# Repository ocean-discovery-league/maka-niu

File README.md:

# maka-niu

"Maka" - Eye, "Niu" - Coconut

Maka Niu, aka the "CocoCam,"  is a low-cost oceanographic camera and sensor platform that enables the exploration of undersea environments using a new pressure-tolerant camera housing and an all-natural, locally sourced, biodegradable buoyancy-control device. The coconut (Cocos nucifera ) can float for over 3,000 miles and still remain viable; as such, it makes an excellent organic platform for deploying scientific apparatus.

Maka Niu is a community-driven project that allows local groups to explore and monitor their marine resources. Based around off-the-shelf single-board computers and readily available microprocessors, Maka Niu is inexpensive to produce, easy to program, and simple to use. Designed as an open platform for scientific education and exploration, it will give classrooms and communities the ability to upload video and sensor data into FathomNet, a centralized database where machine learning algorithms assist with classification of marine species, seabed substrate identification, and accumulated time-series sensor data. This data will be publically available, allowing visualization, sharing, and discussion with policy makers from the local to global levels.

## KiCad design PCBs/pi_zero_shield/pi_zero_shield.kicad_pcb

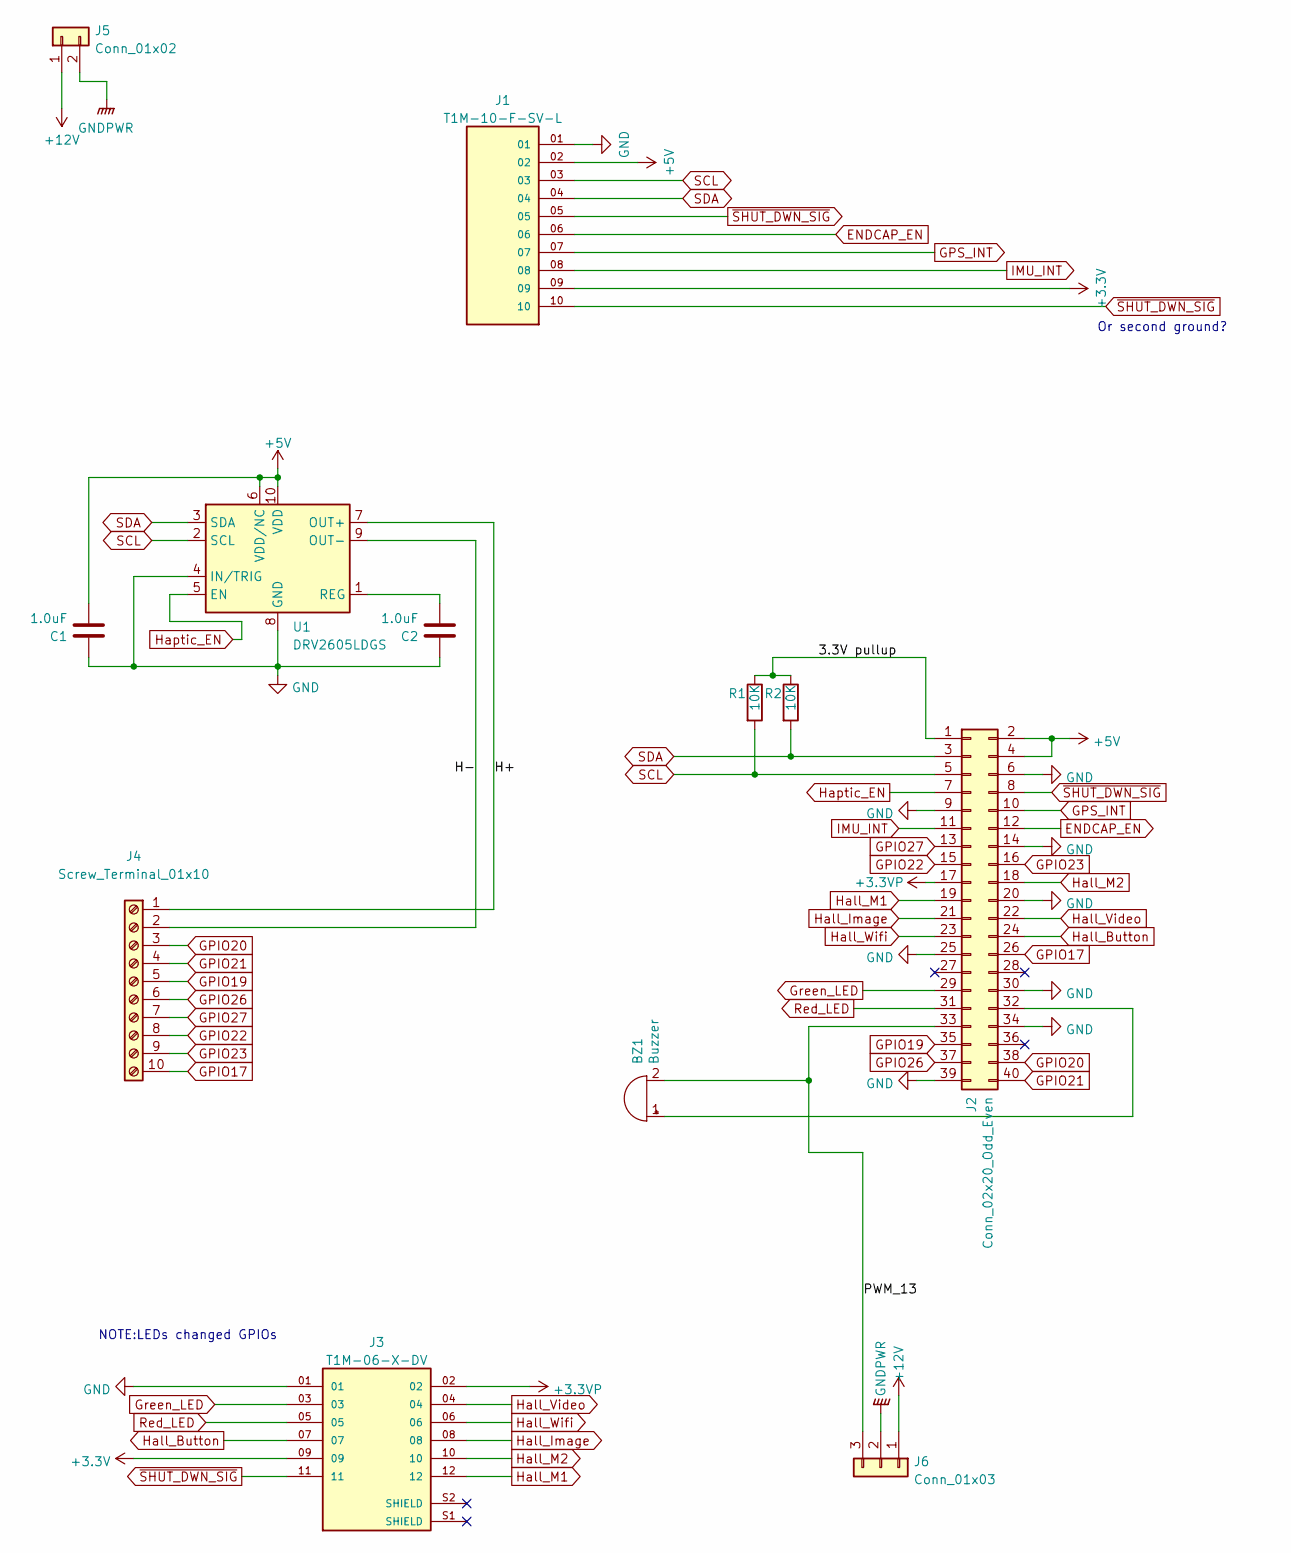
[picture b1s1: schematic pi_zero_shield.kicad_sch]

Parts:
BZ1: Buzzer; Buzzer_12x9.5RM7.6; LCSC C968749
C1, C2: 1.0uF; C_0603_1608Metric; LCSC C90540
J1: T1M-10-F-SV-L; SAMTEC_T1M-10-F-SV-L; Digikey SAM16035-ND
J2: Conn_02x20_Odd_Even; Pi_PinSocket_2x20; Digikey 952-3218-ND
J3: T1M-06-X-DV; SAMTEC_T1M-06-X-DV; Digikey -Get from Samtec
J4: Screw_Terminal_01x10; PinHeader_1x10_P2.54mm_Vertical; Digikey ED10567-ND
J5: Conn_01x02; Molex_Micro-Fit_3.0_43650-0210_1x02-1MP_P3.00mm_Horizontal; Digikey WM6264CT-ND
J6: Conn_01x03; Molex_Micro-Fit_3.0_43650-0310_1x03-1MP_P3.00mm_Horizontal; Digikey WM1886CT-ND
R1, R2: 10K; R_0603_1608Metric; LCSC C25804
U1: DRV2605LDGS; VSSOP-10_3x3mm_P0.5mm; LCSC C527464

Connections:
+3.3VP: J2.17, J3.02
+3V3: J1.09, J3.09
+5V: C1.1, J1.02, J2.2, J2.4, U1.6 (VDD/NC), U1.10 (VDD)
+12V: J5.1, J6.1
/3.3V pullup: J2.1, R1.1, R2.1
/H+: J4.1, U1.7 (OUT+)
/H-: J4.2, U1.9 (OUT-)
/PWM_13: BZ1.2 (+), J2.33, J6.3
ENDCAP_EN: J1.06, J2.12
GND: C1.2, C2.2, J1.01, J2.6, J2.9, J2.14, J2.20, J2.25, J2.30, J2.34, J2.39, J3.01, U1.4 (IN/TRIG), U1.8 (GND)
GNDPWR: J5.2, J6.2
GPIO17: J2.26, J4.10
GPIO19: J2.35, J4.5
GPIO20: J2.38, J4.3
GPIO21: J2.40, J4.4
GPIO22: J2.15, J4.8
GPIO23: J2.16, J4.9
GPIO26: J2.37, J4.6
GPIO27: J2.13, J4.7
GPS_INT: J1.07, J2.10
Green_LED: J2.29, J3.03
Hall_Button: J2.24, J3.07
Hall_Image: J2.21, J3.08
Hall_M1: J2.19, J3.12
Hall_M2: J2.18, J3.10
Hall_Video: J2.22, J3.04
Hall_Wifi: J2.23, J3.06
Haptic_EN: J2.7, U1.5 (EN)
IMU_INT: J1.08, J2.11
unnamed: BZ1.1 (-), J2.32
unnamed: C2.1, U1.1 (REG)
Red_LED: J2.31, J3.05
SCL: J1.03, J2.5, R1.2, U1.2 (SCL)
SDA: J1.04, J2.3, R2.2, U1.3 (SDA)
~SHUT_DWN_SIG: J1.05, J1.10, J2.8, J3.11

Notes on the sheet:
NOTE:LEDs changed GPIOs
Or second ground?

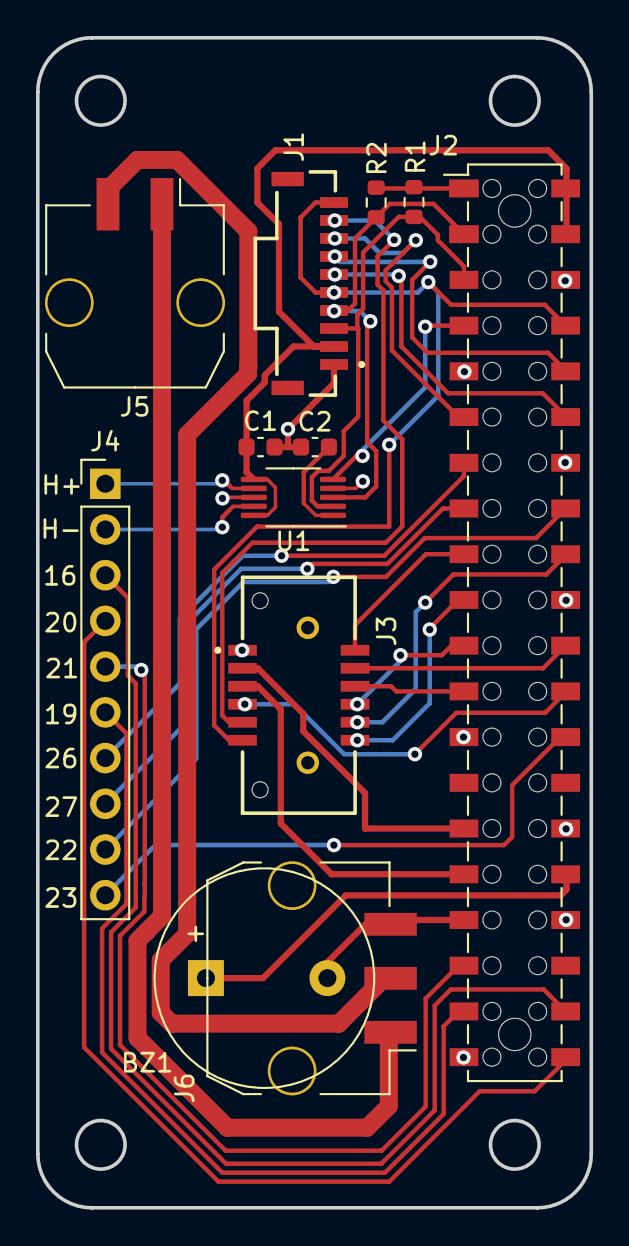
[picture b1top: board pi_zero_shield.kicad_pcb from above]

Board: 2 copper layers, 30.8 x 65.0 mm, 12 parts (0 on the bottom side), 35 nets.

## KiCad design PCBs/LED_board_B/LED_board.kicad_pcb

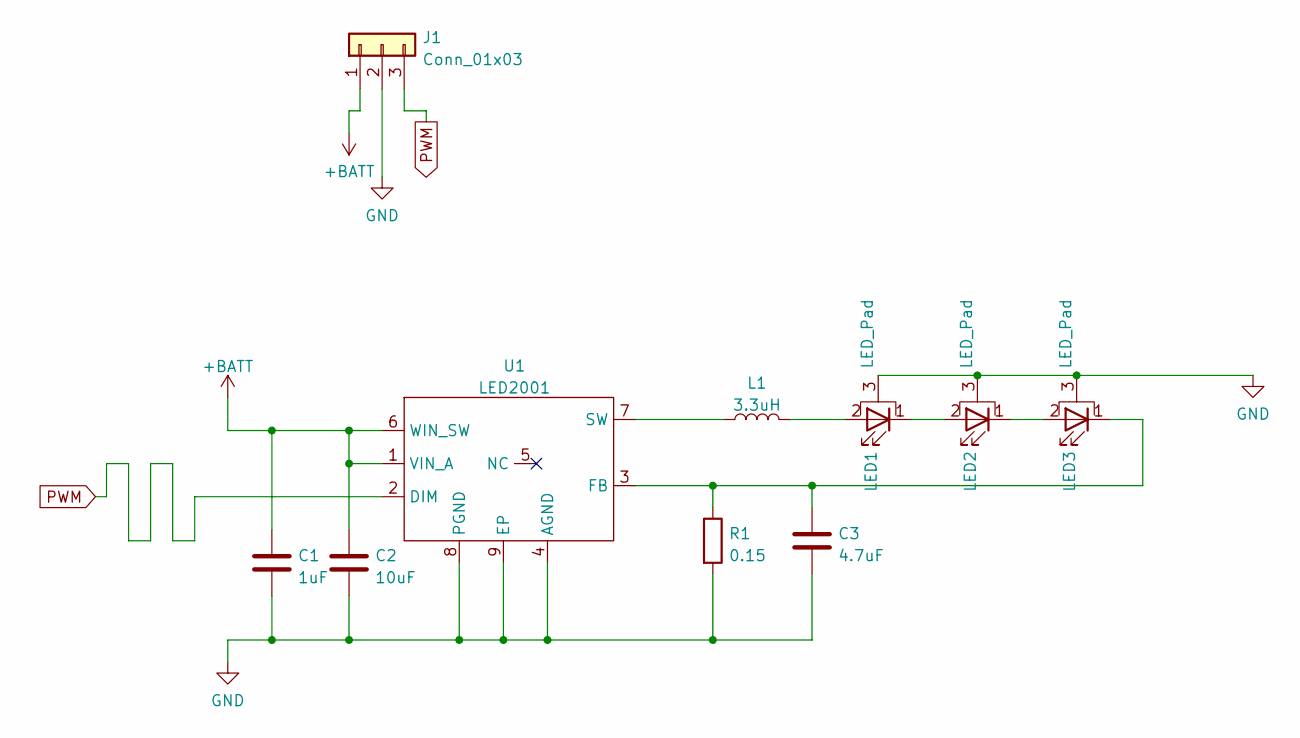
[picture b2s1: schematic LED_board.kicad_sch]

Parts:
C1: 1uF; C_0805_2012Metric; LCSC C28323
C2: 10uF; C_1210_3225Metric; LCSC C170073
C3: 4.7uF; C_1210_3225Metric; LCSC C384711
J1: Conn_01x03; Molex_Micro-Fit_3.0_43650-0324_1x03-1MP_P3.00mm_Vertical; Digikey WM3887CT-ND
L1: 3.3uH; ASWPA8050S; LCSC C340237
LED1, LED2, LED3: LED_Pad; LED_Cree-XHP50_6V; Digikey XMLBWT-00-0000-0000U2050CT-ND
R1: 0.15; R_2512_6332Metric; LCSC C176046
U1: LED2001; HSOP-8-1EP_3.9x4.9mm_P1.27mm_EP2.41x3.1mm; LCSC C2678918

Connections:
+BATT: C1.1, C2.1, J1.1, U1.1 (VIN_A), U1.6 (WIN_SW)
GND: C1.2, C2.2, C3.2, J1.2, LED1.3 (PAD), LED2.3 (PAD), LED3.3 (PAD), R1.2, U1.4 (AGND), U1.8 (PGND), U1.9 (EP)
unnamed: C3.1, LED3.1 (K), R1.1, U1.3 (FB)
unnamed: L1.1, U1.7 (SW)
unnamed: L1.2, LED1.2 (A)
unnamed: LED1.1 (K), LED2.2 (A)
unnamed: LED2.1 (K), LED3.2 (A)
PWM: J1.3, U1.2 (DIM)

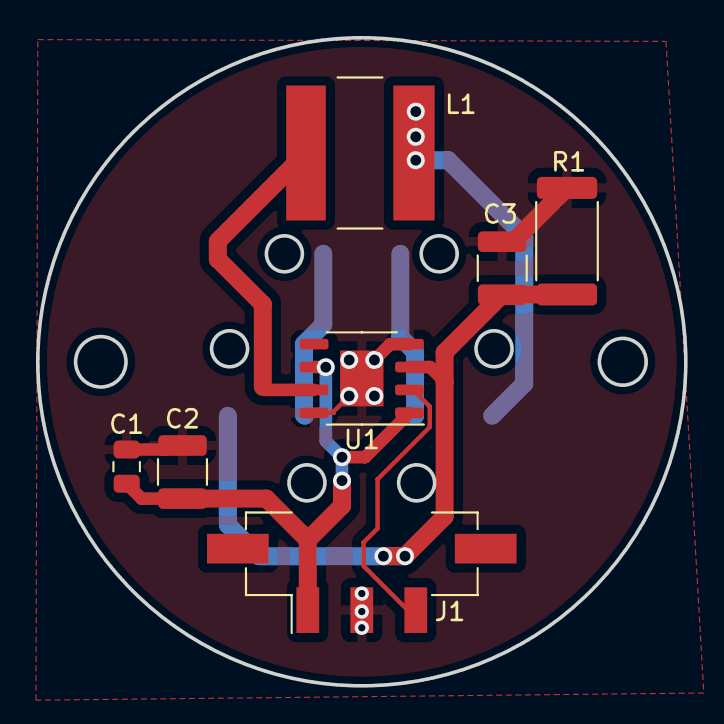
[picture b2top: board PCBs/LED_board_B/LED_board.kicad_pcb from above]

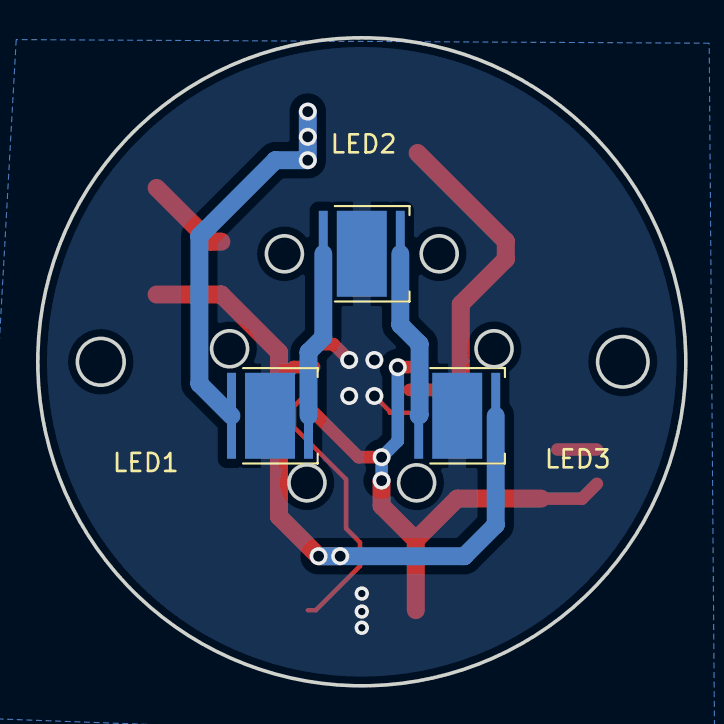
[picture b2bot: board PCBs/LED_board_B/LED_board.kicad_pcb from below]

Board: 2 copper layers, 36.0 x 36.0 mm, 10 parts (3 on the bottom side), 8 nets.

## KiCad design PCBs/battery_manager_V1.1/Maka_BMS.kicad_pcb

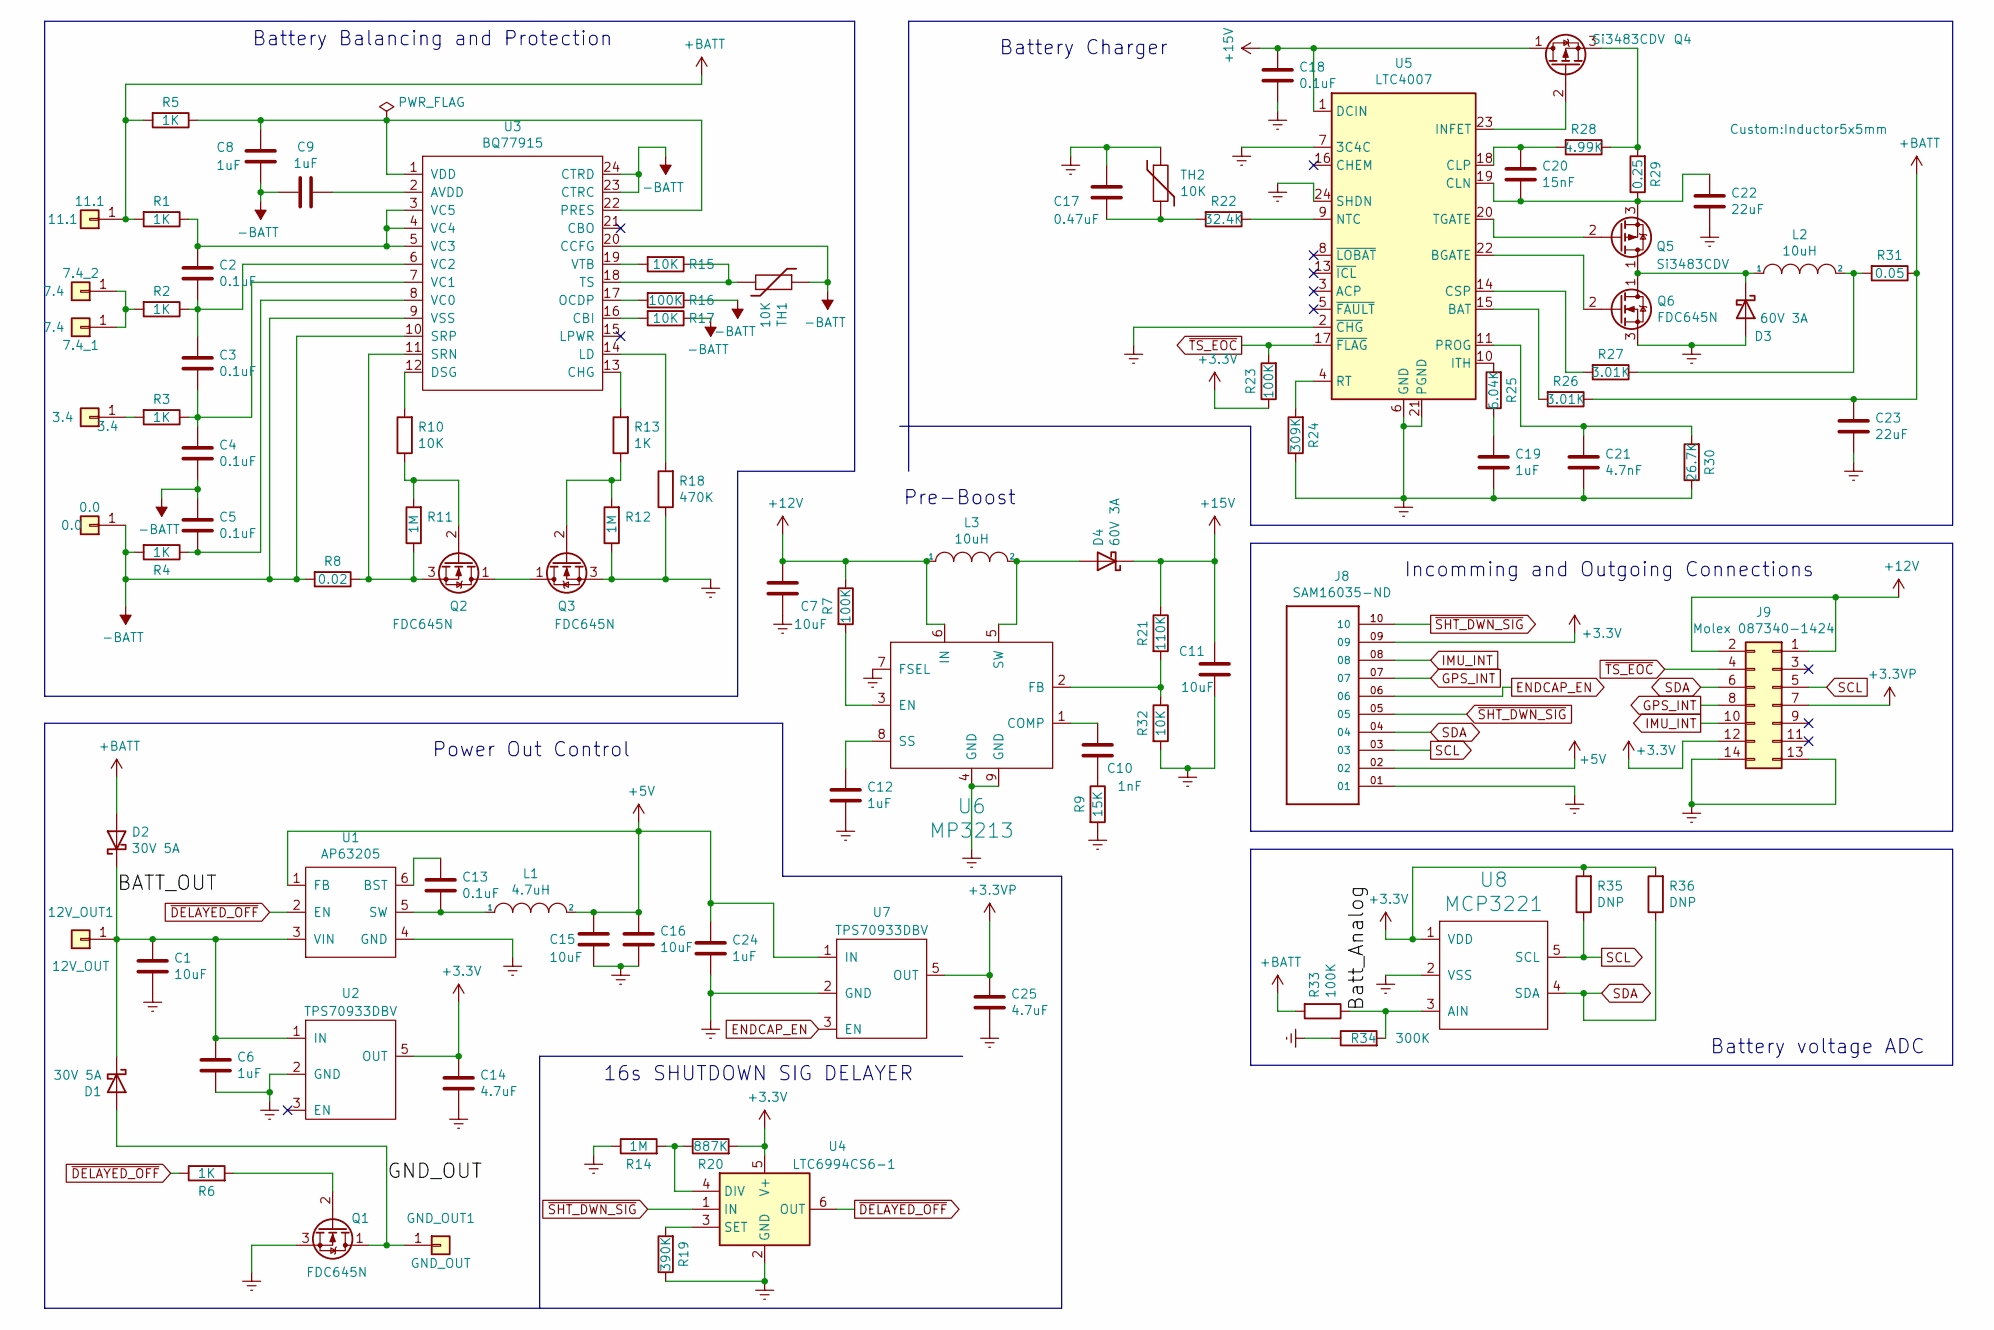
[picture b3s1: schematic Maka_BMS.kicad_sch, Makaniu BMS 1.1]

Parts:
0.0: 0.0; TruHole_Batter_Contact_Pad_with_9mm_clear; Digikey 36-240-ND
3.4: 3.4; TestPoint_THTPad_D1.5mm_Drill0.7mm
7.4_1, 7.4_2: 7.4; TruHole_Batter_Contact_Pad_with_9mm_clear; Digikey 36-240-ND
11.1: 11.1; TestPoint_THTPad_D1.5mm_Drill0.7mm
12V_OUT1: 12V_OUT; TestPoint_THTPad_D1.5mm_Drill0.7mm
C1, C7, C11, C15, C16: 10uF; C_0603_1608Metric; Digikey 490-7202-1-ND
C2, C3, C4, C5, C13, C18: 0.1uF; C_0402_1005Metric; Digikey 732-7495-1-ND
C6, C8, C9, C12, C19, C24: 1uF; C_0402_1005Metric; Digikey 490-10017-1-ND
C10: 1nF; C_0402_1005Metric; Digikey 478-1101-2-ND
C14, C25: 4.7uF; C_0603_1608Metric; Digikey 1276-1900-1-ND
C17: 0.47uF; C_0402_1005Metric; Digikey 490-12269-1-ND
C20: 15nF; C_0402_1005Metric; Digikey 311-1713-1-ND
C21: 4.7nF; C_0402_1005Metric; Digikey 311-1039-1-ND
C22, C23: 22uF; C_0603_1608Metric; Digikey 1276-7076-1-ND
D1, D2: 30V 5A; D_SMA; Digikey SK56A-LTPMSTR-ND
D3, D4: 60V 3A; D_SOD-123EP; Digikey SSA36CT-ND
GND_OUT1: GND_OUT; TestPoint_THTPad_D1.5mm_Drill0.7mm
J8: ‎SAM16035-ND‎; SAMTEC_T1M-10-F-SH-L-K; Digikey SAM11993-ND
J9: Molex 087340-1424; Molex_87340-1424_B; Digikey 23-0873401424-ND
L1: 4.7uH; L_1008_2520Metric; Digikey 490-10651-1-ND
L2, L3: 10uH; Inductor5x5mm; Digikey 1589-MPL-SE6040-100CT-ND
Q1, Q2, Q3, Q6: FDC645N; SOT-23-6_mosfet; Digikey FDC655BNCT-ND
Q4, Q5: Si3483CDV; SOT-23-6_mosfet; Digikey CPH6350-TL-WOSCT-ND
R1, R2, R3, R4, R5, R6, R13: 1K; R_0402_1005Metric; Digikey YAG1234CT-ND
R7, R16, R23, R33: 100K; R_0402_1005Metric; Digikey 311-100KLRCT-ND
R8: 0.02; R_1206_3216Metric; Digikey WSLP-.02CT-ND
R9: 15K; R_0402_1005Metric; Digikey 311-15.0KLRTR-ND
R10, R15, R17, R32: 10K; R_0402_1005Metric; Digikey 311-10.0KLRCT-ND
R11, R12, R14: 1M; R_0402_1005Metric; Digikey 311-1.00MLRCT-ND
R18: 470K; R_0402_1005Metric; Digikey 311-470KJRCT-ND
R19: 390K; R_0402_1005Metric; Digikey YAG3143CT-ND
R20: 887K; R_0402_1005Metric; Digikey YAG5696CT-ND
R21: 110K; R_0402_1005Metric; Digikey 311-110KLRCT-ND
R22: 32.4K; R_0402_1005Metric; Digikey YAG3119CT-ND
R24: 309K; R_0402_1005Metric; Digikey YAG3108CT-ND
R25: 6.04K; R_0402_1005Metric; Digikey YAG2293CT-ND
R26, R27: 3.01K; R_0402_1005Metric; Digikey 311-3.01KLRCT-ND
R28: 4.99K; R_0402_1005Metric; Digikey YAG1447CT-ND
R29: 0.25; R_1206_3216Metric; Digikey 311-0.25ANCT-ND
R30: 26.7K; R_0402_1005Metric; Digikey YAG3081CT-ND
R31: 0.05; R_1206_3216Metric; Digikey MCS1632R050FERCT-ND
R34: 300K; R_0402_1005Metric; Digikey 311-300KLRCT-ND
R35, R36: DNP; R_0402_1005Metric
TH1: 10K; R_0402_1005Metric; Digikey 495-5814-1-ND
TH2: 10K; R_0402_1005Metric; Digikey 311-10.0KLRCT-ND
U1: AP63205; TSOT-23-6; Digikey AP63205WU-7DICT-ND
U2, U7: TPS70933DBV; SOT-23-5; Digikey 497-6979-1-ND
U3: BQ77915; TSSOP-24_4.4x7.8mm_P0.65mm; Digikey 296-50995-1-ND
U4: LTC6994CS6-1; TSOT-23-6; Digikey LTC6994CS6-1#TRMPBFCT-ND
U5: LTC4007; SSOP-24_3.9x8.7mm_P0.635mm; Digikey LTC4007EGN#PBF-ND
U6: MP3213; MSOP-8-1EP_3x3mm_P0.65mm_EP1.95x2.15mm; Digikey 1589-1626-1-ND
U8: MCP3221; SOT-23-5; LCSC C36310

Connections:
+3.3VP: C25.2, J9.7, U7.5 (OUT)
+3V3: C14.2, J8.09, J9.12, R20.2, R23.1, R35.2, R36.2, U2.5 (OUT), U4.5 (V+), U8.1 (VDD)
+5V: C15.2, C16.2, C24.2, J8.02, L1.2, U1.1 (FB), U7.1 (IN)
+12V: C7.1, J9.1, J9.2, L3.1, R7.1, U6.6 (IN)
+15V: C11.1, C18.2, D4.1 (K), Q4.1 (D), R21.1, U5.1 (DCIN)
+BATT: 11.1.1, C23.2, D2.2 (A), R1.2, R5.2, R26.1, R31.1, R33.2
-BATT: 0.0.1, C4.1, C5.2, C8.1, C9.2, R4.2, R8.2, R16.1, R17.1, TH1.1, U3.9 (VSS), U3.10 (SRP), U3.20 (CCFG), U3.23 (CTRC), U3.24 (CTRD)
/BATT_OUT: 12V_OUT1.1, C1.2, C6.2, D1.1 (K), D2.1 (K), U1.3 (VIN), U2.1 (IN)
/Batt_Analog: R33.1, R34.2, U8.3 (AIN)
/GND_OUT: D1.2 (A), GND_OUT1.1, Q1.1 (D)
ENDCAP_EN: J8.06, U7.3 (EN)
Earth: C1.1, C6.1, C7.2, C11.2, C12.1, C14.1, C15.1, C16.1, C17.2, C18.1, C19.1, C21.1, C22.1, C23.1, C24.1, C25.1, D3.2 (A), J8.01, J9.13, J9.14, Q1.3 (S), Q3.3 (S), Q6.3 (S), R9.2, R12.1, R14.1, R18.1, R19.1, R24.1, R30.1, R32.2, R34.1, TH2.1, U1.4 (GND), U2.2 (GND), U4.2 (GND), U5.2 (~CHG), U5.6 (GND), U5.7 (3C4C), U5.21 (PGND), U5.24 (SHDN), U6.4 (GND), U6.7 (FSEL), U6.9 (GND), U7.2 (GND), U8.2 (VSS)
GPS_INT: J8.07, J9.8
IMU_INT: J8.08, J9.10
unnamed: 3.4.1, R3.2
unnamed: 7.4_1.1, 7.4_2.1, R2.2
unnamed: C2.1, C3.2, R2.1, U3.6 (VC2)
unnamed: C2.2, R1.1, U3.3 (VC5), U3.4 (VC4), U3.5 (VC3)
unnamed: C3.1, C4.2, R3.1, U3.7 (VC1)
unnamed: C5.1, R4.1, U3.8 (VC0)
unnamed: C8.2, R5.1, U3.1 (VDD), U3.22 (PRES)
unnamed: C9.1, U3.2 (AVDD)
unnamed: C10.1, U6.1 (COMP)
unnamed: C10.2, R9.1
unnamed: C12.2, U6.8 (SS)
unnamed: C13.1, L1.1, U1.5 (SW)
unnamed: C13.2, U1.6 (BST)
unnamed: C17.1, R22.2, TH2.2
unnamed: C19.2, R25.1
unnamed: C20.1, C22.2, Q5.3 (S), R29.1, U5.19 (CLN)
unnamed: C20.2, R28.2, U5.18 (CLP)
unnamed: C21.2, R30.2, U5.11 (PROG)
unnamed: D4.2 (A), L3.2, U6.5 (SW)
unnamed: D3.1 (K), L2.1, Q5.1 (D), Q6.1 (D)
unnamed: L2.2, R27.1, R31.2
unnamed: Q1.2 (G), R6.2
unnamed: Q2.1 (D), Q3.1 (D)
unnamed: Q2.2 (G), R10.1, R11.2
unnamed: Q2.3 (S), R8.1, R11.1, U3.11 (SRN)
unnamed: Q3.2 (G), R12.2, R13.1
unnamed: Q4.2 (G), U5.23 (INFET)
unnamed: Q4.3 (S), R28.1, R29.2
unnamed: Q5.2 (G), U5.20 (TGATE)
unnamed: Q6.2 (G), U5.22 (BGATE)
unnamed: R7.2, U6.3 (EN)
unnamed: R10.2, U3.12 (DSG)
unnamed: R13.2, U3.13 (CHG)
unnamed: R14.2, R20.1, U4.4 (DIV)
unnamed: R15.1, TH1.2, U3.18 (TS)
unnamed: R15.2, U3.19 (VTB)
unnamed: R16.2, U3.17 (OCDP)
unnamed: R17.2, U3.16 (CBI)
unnamed: R18.2, U3.14 (LD)
unnamed: R19.2, U4.3 (SET)
unnamed: R21.2, R32.1, U6.2 (FB)
unnamed: R22.1, U5.9 (NTC)
unnamed: R24.2, U5.4 (RT)
unnamed: R25.2, U5.10 (ITH)
unnamed: R27.2, U5.14 (CSP)
unnamed: R26.2, U5.15 (BAT)
SCL: J8.03, J9.5, R35.1, U8.5 (SCL)
SDA: J8.04, J9.6, R36.1, U8.4 (SDA)
~DELAYED_OFF: R6.1, U1.2 (EN), U4.6 (OUT)
~SHT_DWN_SIG: J8.05, J8.10, U4.1 (IN)
~TS_EOC: J9.4, R23.2, U5.17 (~FLAG)

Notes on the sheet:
Power Out Control
16s SHUTDOWN SIG DELAYER
Battery voltage ADC
Pre-Boost
Battery Charger
Battery Balancing and Protection
Incomming and Outgoing Connections

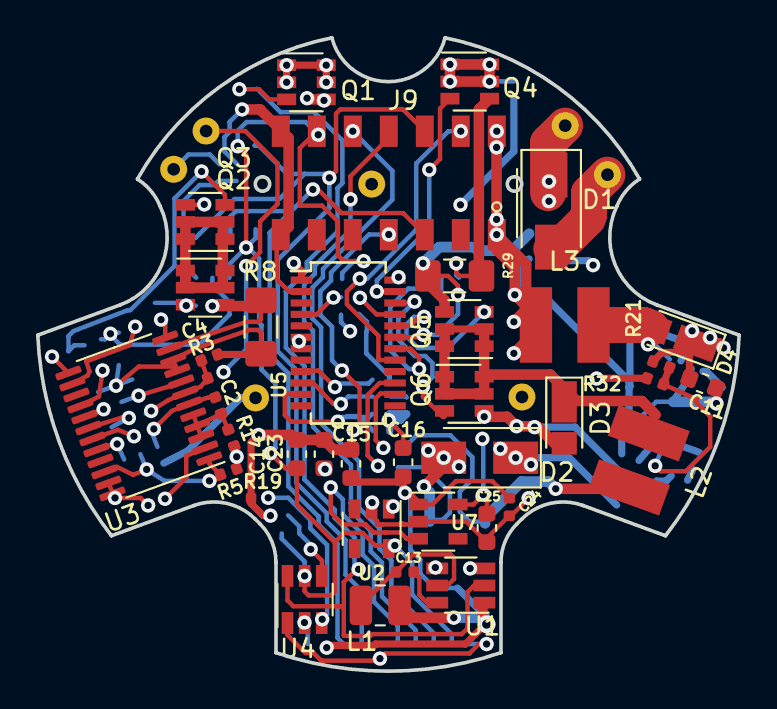
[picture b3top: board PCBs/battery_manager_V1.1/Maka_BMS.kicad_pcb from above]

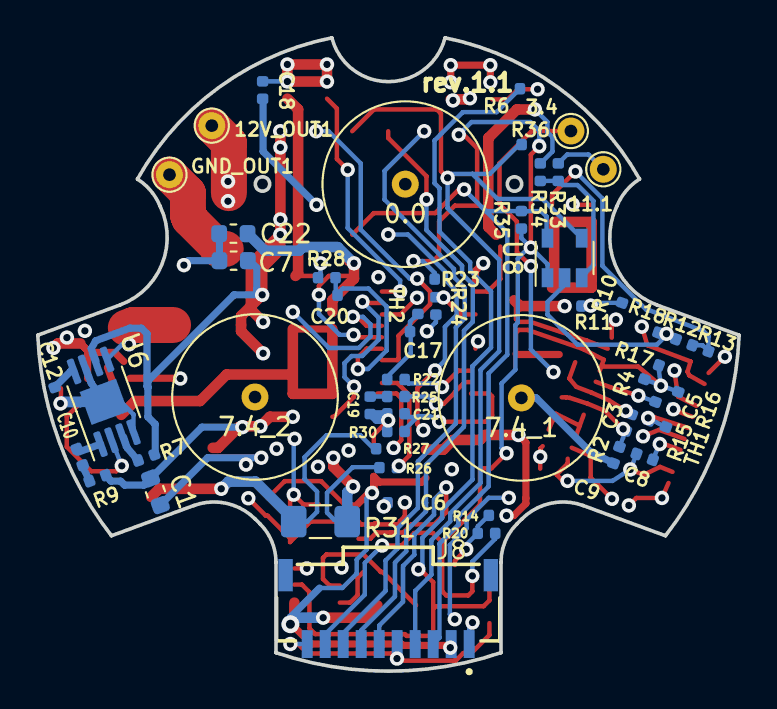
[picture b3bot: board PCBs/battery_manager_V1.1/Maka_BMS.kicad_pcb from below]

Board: 4 copper layers, 39.0 x 35.2 mm, 93 parts (55 on the bottom side), 65 nets.

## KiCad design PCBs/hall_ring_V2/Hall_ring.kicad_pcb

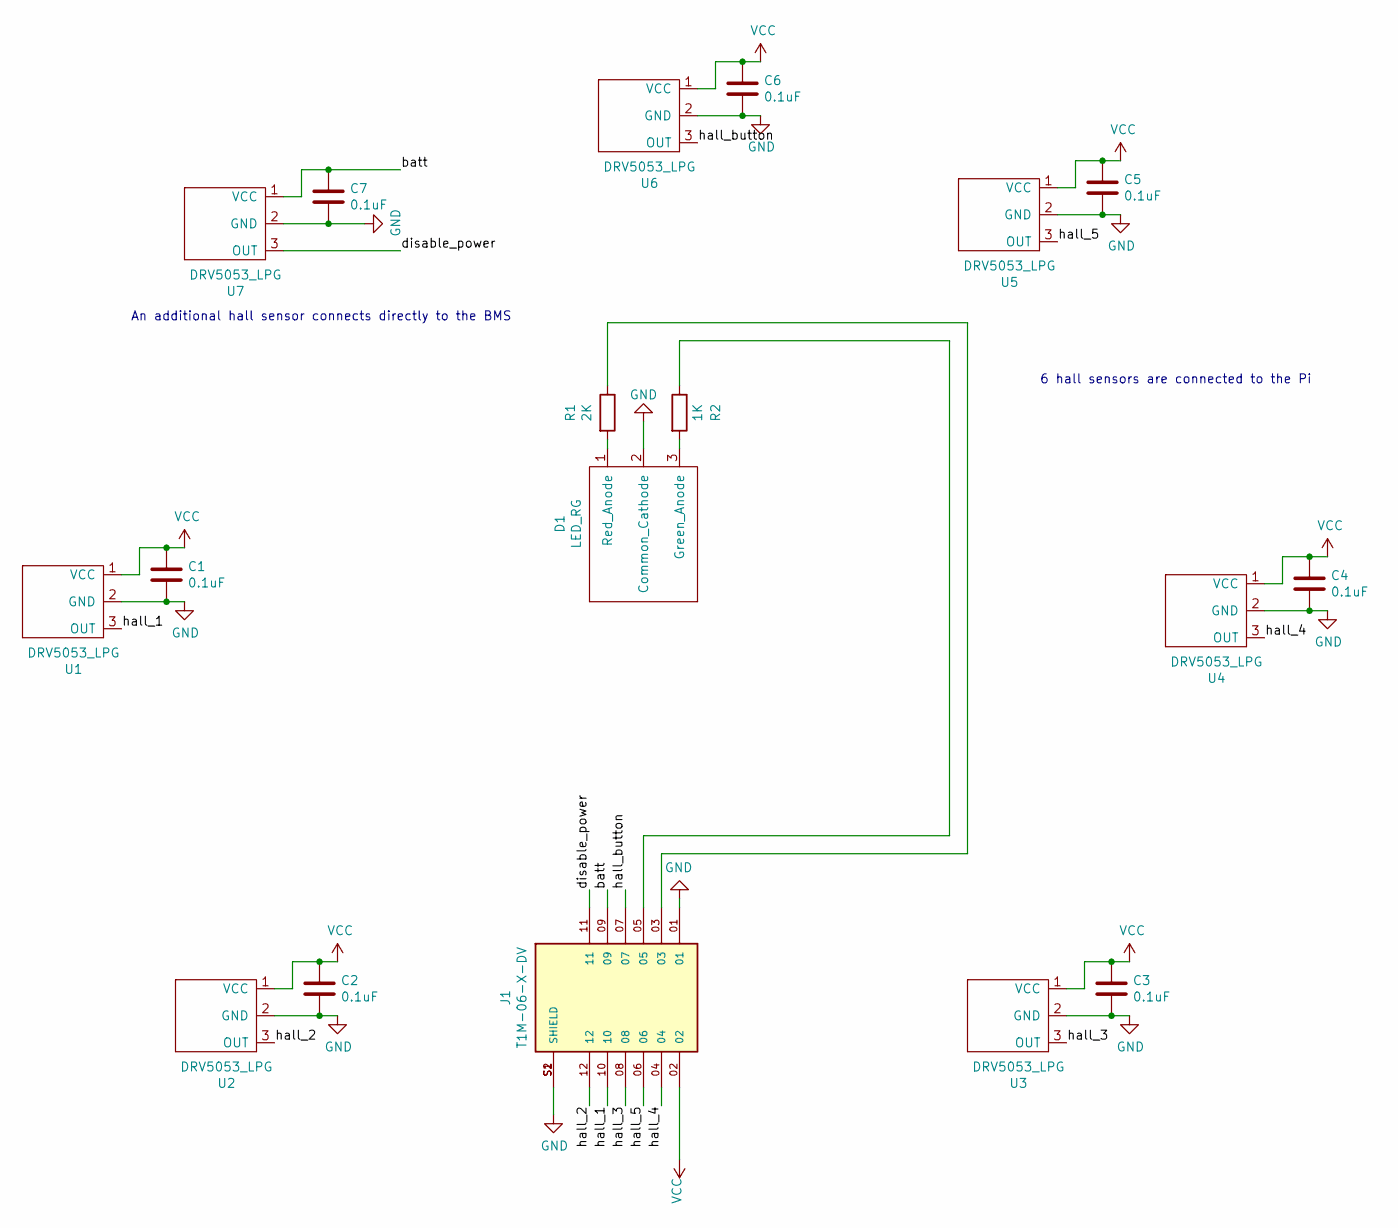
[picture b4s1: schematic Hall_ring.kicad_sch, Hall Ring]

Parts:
C1, C2, C3, C4, C5, C6, C7: 0.1uF; C_0402_1005Metric; Digikey 1276-1043-2-ND
D1: LED_RG; PinHeader_1x03_P2.00mm_Vertical; Digikey 160-1939-ND
J1: T1M-06-X-DV; SAMTEC_T1M-06-X-DV; Digikey ~ Get from Samtec
R1: 2K; R_0402_1005Metric; Digikey CR0402-FX-2001GLFCT-ND
R2: 1K; R_0402_1005Metric; Digikey RMCF0402FT1K00CT-ND
U1, U2, U3, U4, U5, U6, U7: DRV5053_LPG; TO-92Flat; Digikey 296-DRV5032DULPGMCT-ND

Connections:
/batt: C7.1, J1.09, U7.1 (VCC)
/disable_power: J1.11, U7.3 (OUT)
/hall_1: J1.10, U1.3 (OUT)
/hall_2: J1.12, U2.3 (OUT)
/hall_3: J1.08, U3.3 (OUT)
/hall_4: J1.04, U4.3 (OUT)
/hall_5: J1.06, U5.3 (OUT)
/hall_button: J1.07, U6.3 (OUT)
GND: C1.2, C2.2, C3.2, C4.2, C5.2, C6.2, C7.2, D1.2 (Common_Cathode), J1.01, J1.S1 (SHIELD), J1.S2 (SHIELD), U1.2 (GND), U2.2 (GND), U3.2 (GND), U4.2 (GND), U5.2 (GND), U6.2 (GND), U7.2 (GND)
unnamed: D1.1 (Red_Anode), R1.2
unnamed: D1.3 (Green_Anode), R2.2
unnamed: J1.03, R1.1
unnamed: J1.05, R2.1
VCC: C1.1, C2.1, C3.1, C4.1, C5.1, C6.1, J1.02, U1.1 (VCC), U2.1 (VCC), U3.1 (VCC), U4.1 (VCC), U5.1 (VCC), U6.1 (VCC)

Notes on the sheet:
6 hall sensors are connected to the Pi
An additional hall sensor connects directly to the BMS

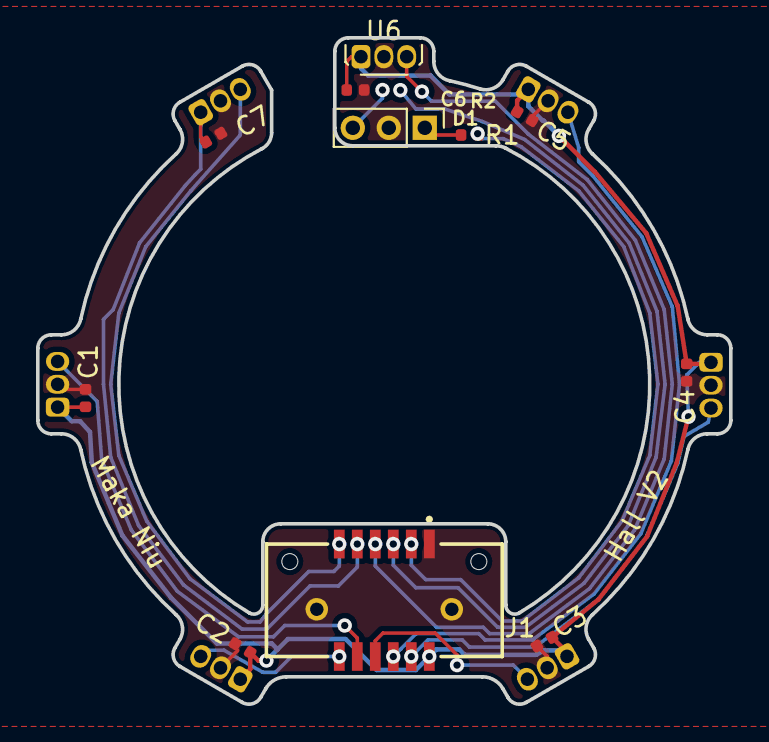
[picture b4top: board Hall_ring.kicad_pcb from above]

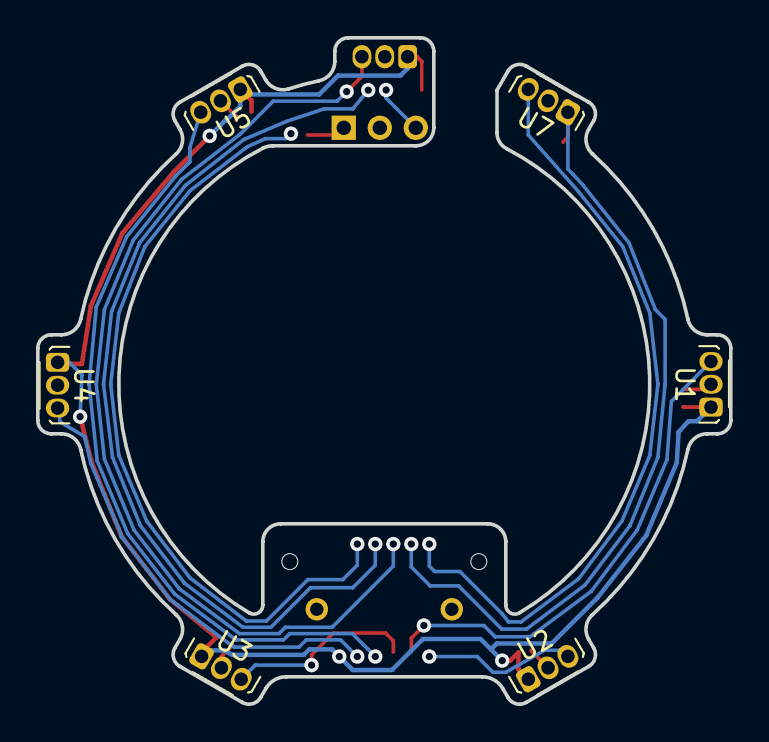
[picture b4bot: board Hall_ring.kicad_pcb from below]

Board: 2 copper layers, 38.5 x 37.0 mm, 18 parts (6 on the bottom side), 14 nets.

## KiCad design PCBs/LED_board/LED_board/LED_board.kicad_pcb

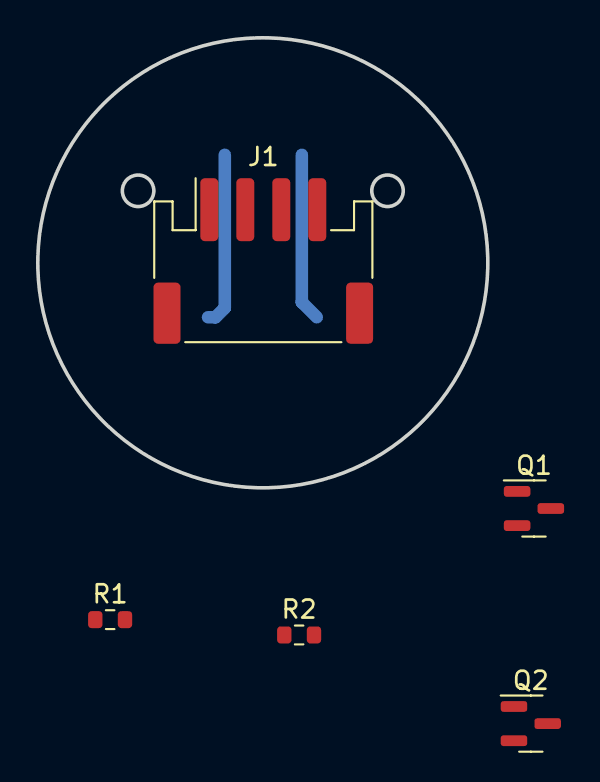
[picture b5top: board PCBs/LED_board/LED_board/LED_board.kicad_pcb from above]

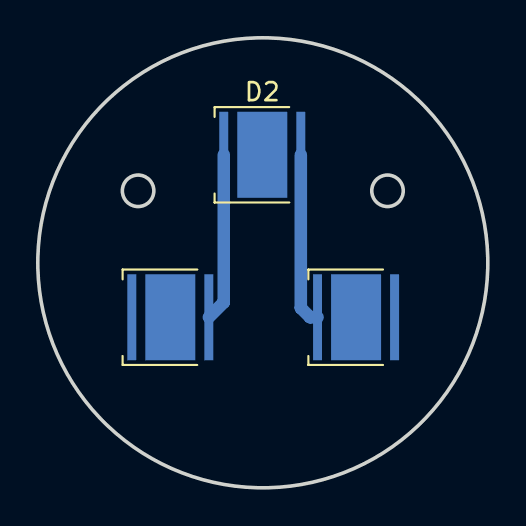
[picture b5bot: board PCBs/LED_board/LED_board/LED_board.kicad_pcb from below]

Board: 2 copper layers, 25.0 x 25.0 mm, 8 parts (3 on the bottom side), 7 nets.

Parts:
D1, D2, D3: LED_Pad; LED_Cree-XHP50_6V
J1: S4B-PH-SM4; JST_PH_S4B-PH-SM4-TB_1x04-1MP_P2.00mm_Horizontal
Q1: Q_NPN_BCE; SOT-23
Q2: Q_NMOS_DGS; SOT-23
R1, R2: R; R_0603_1608Metric

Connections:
+BATT: D1.2 (A), J1.2, R1.1
GND: J1.1, Q1.3 (E), R2.2
unnamed: D1.1 (K), D2.2 (A)
unnamed: D2.1 (K), D3.2 (A)
unnamed: D3.1 (K), Q2.1 (D)
unnamed: Q1.1 (B), Q2.3 (S), R2.1
unnamed: Q1.2 (C), Q2.2 (G), R1.2
